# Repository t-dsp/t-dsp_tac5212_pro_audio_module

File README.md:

# T-DSP TAC5212 Pro Audio Module

**Part of the [T-DSP](https://t-dsp.com) open modular audio platform.**

A compact (50mm x 34.5mm) stereo audio codec module built around the **Texas Instruments TAC5212** high-performance audio codec.

| | |
|:---:|:---:|
|  |  |
|  |  |

**[View 3D Render Gallery](https://t-dsp.github.io/t-dsp_tac5212_pro_audio_module/gallery.html)** -- interactive slideshow of all board views

## About T-DSP

T-DSP is an open modular audio platform designed for musicians, engineers, and developers who want powerful digital signal processing in a flexible, hackable format. Built around the [Teensy](https://www.pjrc.com/teensy/) microcontroller and the [Teensy Audio Library](https://www.pjrc.com/teensy/td_libs_Audio.html), T-DSP combines studio-quality audio with a growing library of open-source modules for mixing, synthesis, effects, and more.

Whether you're building a custom digital mixer, crafting a unique instrument, or prototyping audio products, T-DSP gives you the tools to bring your ideas to life.

Join the community, contribute to the library, or grab a module and start patching. Learn more at [t-dsp.com](https://t-dsp.com).

## Overview

This codec module provides stereo ADC and DAC conversion and is one of the core building blocks of the T-DSP platform. It is designed as a **chip-on-board module** -- a complete, self-contained audio codec that solders directly onto a user-designed backplane PCB, just like any other component. A KiCad footprint is provided so you can drop the module into your own backplane design, add whatever jacks and connectors your application needs, and build a custom audio device without dealing with codec layout or analog design.

## Audio Capabilities

### Inputs (2 differential pairs)
- Line-level (consumer -10dBV or professional +4dBu)
- Instrument-level (guitar/bass) with external preamp/buffer (preamp and buffer modules are on the T-DSP project roadmap)
- Microphone (dynamic, with up to 12dB analog channel gain and additional digital gain)
- Programmable input impedance (5k/10k/40k ohm), DC-coupled. Optional 100k ohm bias resistors on board.
- 2 VRMS full-scale differential input

### Outputs (2 differential pairs)
- Headphone drive (16-300 ohm, 62.5mW @ 16 ohm, ~31mW @ 32 ohm)
- Consumer line out (-10dBV)
- Professional balanced output (+4dBu)
- 10 ohm output impedance, 2 VRMS differential output

## Digital Interface

- **I2S/PCM** audio data (DIN, DOUT, BCLK, LRCK, MCLK)
- **I2C** control bus for codec register configuration
- **GPIO** pins for additional control and sensing

The T-DSP platform is developed with [Teensy](https://www.pjrc.com/teensy/) and the [Teensy Audio Library](https://www.pjrc.com/teensy/td_libs_Audio.html), but the module uses standard I2S and I2C interfaces and can work with any compatible microcontroller or DSP platform.

## Modular Architecture

The module connects to your backplane via **2.54mm (0.1") header pins** (52 pins total), organized into functional groups. Headers can be male/female for a removable connection, or soldered permanently with straight pins:

- **DSP IO** (20 pins) -- digital audio (I2S), I2C control, MCLK, and power. Also available as a 20-pin ribbon header for off-board connection via standard ribbon cable.
- **Analog IO** (16 pins) -- stereo input and output pairs with analog ground references.
- **GPIO** (8 pins) -- additional I2C, general-purpose IO, and digital ground.
- **Power** (8 pins) -- 5V, 3.3V, MIC_BIAS, and ground lines.

### Backplane Integration

A KiCad footprint for the module is included in `/lib_fp/`, allowing you to import it directly into your own backplane PCB design. You handle the jacks, connectors, and mechanical layout on your backplane -- the module takes care of codec, filtering, and power regulation.

**Example backplanes built with the T-DSP module:**

### Module part (backplane)

Same method as the T-DSP core and the other modules: on a backplane the module is one part, **A1 `T-DSP_TAC5212`**
(`lib_sch/t-dsp_tac5212_pro_audio_module.kicad_sym`), with footprint `t-dsp_tac5212_pro_audio_module:T-DSP_TAC5212_Socket`
(`lib_fp/t-dsp_tac5212_pro_audio_module.pretty`, origin = module top-left, module outline on silk). Module 41.34 x 26.46 mm.
The module board itself keeps its own footprint (`board_outline108`, pads 1-52); the socket has the same pads, renumbered:

| Unit | Header | Pins | Module pads |
|---|---|---|---|
| A | J1 DSP IO (2x10, left edge) | 1 EN, 3 5V, 4 3V3_IO, 7 DIN, 9 DOUT, 11 BCLK, 13 LRCK, 15 DSP_SDA, 17 DSP_SCL, 19 MCLK, even pins GNDD (2, 5 NC) | 1-20 |
| B | J2 analog (2x9, top edge) | 1/3 OUT1P/M, 5/7 OUT2P/M, 9/11 IN1P/M, 13/15 IN2P/M, 17 MICBIAS, even pins AGND | 21-36, 48 |
| C | J3 codec I2C / GPIO (1x8, bottom edge) | 1 SCL, 2 SDA, 3 GNDD, 4 GPIO1, 5 GPIO2, 6 GPO1, 7 GPI1, 8 GNDD | 37-44 |
| D | H mounting holes (plated, 2.2 mm, M2) | H1 / H2 AGND side, H3 / H4 DGND side | 49-52 |

All header pins sit on one 2.54 mm grid (the socket snaps the module's pads by 0.01 mm or less). The four M2
standoffs carry the module. Generated by `scripts/build_tac5212_lib.py`.

### Multi-Module Chaining

Because the digital outputs are buffered on each module, multiple modules can run together on the same digital bus. You can daisy-chain modules in two ways:

- **On the backplane** -- route the digital bus as board traces between multiple module footprints.
- **Via ribbon cable** -- use a ribbon cable with multiple taps to connect up to 4 modules per chain.

System designers only need to focus on analog signal routing. The buffered digital bus works reliably over longer distances and across many modules.

## On-Board Circuitry

- LDO regulator for clean 3.3V analog power
- Buffered digital outputs for reliable backplane distribution
- TVS protection on audio outputs
- Ferrite bead RF filtering on audio inputs
- Solder jumpers for I2C address configuration
- Power indicator LED

The T-DSP platform has gone through several design iterations. The bench prototype below is from an earlier version of the project -- a different module architecture that helped shape the current design.

## Project Files

| Directory | Contents |
|-----------|----------|
| `/3d_models/` | 3D models for PCB components and enclosure |
| `/documentation/` | TAC5212 datasheets, [schematic PDF](documentation/t-dsp-tac5212-schematic.pdf), [footprint drawing](documentation/t-dsp-tac5212-footprint.pdf), and [3D model (STL)](documentation/t-dsp_tac5212_pro_audio_module.stl). View online: [schematic](https://kicanvas.org/?github=https://github.com/t-dsp/t-dsp_tac5212_pro_audio_module/blob/main/t-dsp_tac5212_pro_audio_module.kicad_sch) and [PCB layout](https://kicanvas.org/?github=https://github.com/t-dsp/t-dsp_tac5212_pro_audio_module/blob/main/t-dsp_tac5212_pro_audio_module.kicad_pcb) via KiCanvas |
| `/lib_fp/` | Custom KiCad footprint libraries |
| `/lib_sch/` | Custom KiCad schematic symbol libraries |
| `/pages/` | [3D Render Gallery](https://t-dsp.github.io/t-dsp_tac5212_pro_audio_module/gallery.html), [Interactive BOM](https://t-dsp.github.io/t-dsp_tac5212_pro_audio_module/ibom.html) |
| `/scripts/` | LCSC enrichment and BOM verification scripts |

## Building Manufacturing Files

Manufacturing files (gerbers, drill, BOMs, CPL, interactive BOM) are generated automatically by [KiBot](https://github.com/INTI-CMNB/KiBot) via GitHub Actions on every push to `main`. Download the ZIP from the **Actions** tab or from **Releases**.

The ZIP includes:
- Gerbers and drill files for any PCB fabricator
- JLCPCB BOM (`*_bom_JLCPCB.csv`) with LCSC part numbers
- Generic BOM (`*_bom_generic.csv`) with manufacturer part numbers
- Pick and place / CPL file
- Schematic PDF and PCB layout PDF
- Interactive BOM (also deployed live: [view iBOM](https://t-dsp.github.io/t-dsp_tac5212_pro_audio_module/ibom.html))

To build locally, install [Docker](https://www.docker.com/) and run:

```powershell
docker run --rm -v "${PWD}:/workspace" -w /workspace ghcr.io/inti-cmnb/kicad9_auto:latest kibot -c .kibot.yaml -b t-dsp_tac5212_pro_audio_module.kicad_pcb -e t-dsp_tac5212_pro_audio_module.kicad_sch -d manufacturing
```

Output files appear in `manufacturing/t-dsp_tac5212_pro_audio_module/`.

## Related Projects

Browse all T-DSP modules and backplanes on the [T-DSP GitHub organization](https://github.com/orgs/t-dsp/repositories).

## Status

This revision has not yet been built. The previous board was functional but had a few signal routing errors and needed a redesign of the analog output stage for low-impedance headphone drive. Those issues have been addressed in the current design.

If you build one, we'd love to hear how it goes -- please open an issue or reach out with your findings.

## Contact

For consulting, custom backplane design, or commercial licensing inquiries, reach out via [LinkedIn](https://linkedin.com/in/jayshoe).

## License

This project is licensed under the [Creative Commons Attribution-NonCommercial-ShareAlike 4.0 International (CC BY-NC-SA 4.0)](https://creativecommons.org/licenses/by-nc-sa/4.0/).

You are free to share and adapt this work for non-commercial purposes, as long as you give appropriate credit and distribute any derivatives under the same license.

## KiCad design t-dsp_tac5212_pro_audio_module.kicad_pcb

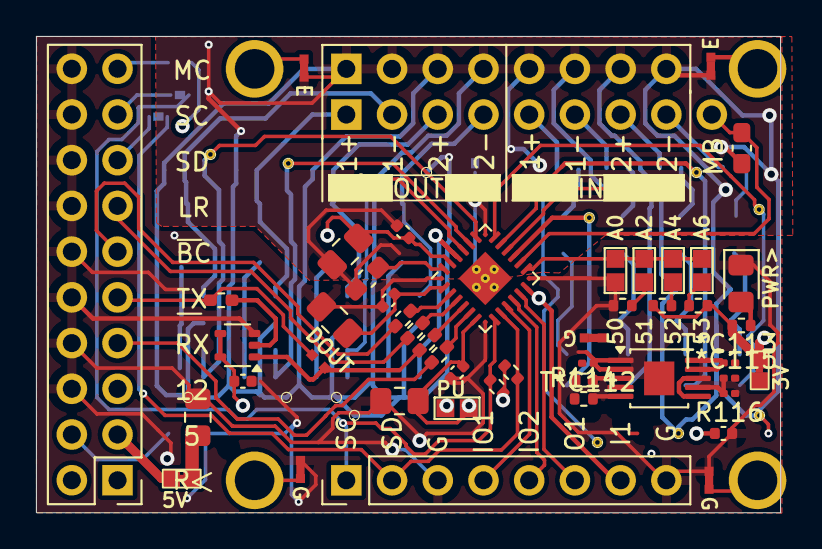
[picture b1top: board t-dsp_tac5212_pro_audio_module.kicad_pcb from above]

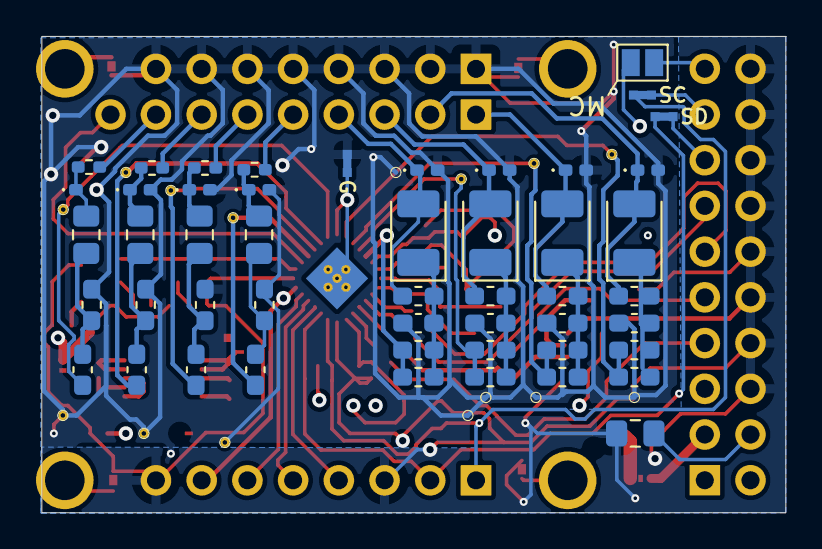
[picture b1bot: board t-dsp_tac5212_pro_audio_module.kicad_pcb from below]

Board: 4 copper layers, 41.3 x 26.5 mm, 117 parts (64 on the bottom side), 72 nets.

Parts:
ADD108: 0x50 | 0xA0; SolderJumper-2_Open_Pad0.5x1.0mm_ADDR
ADD110: 0x52 | 0xA4; SolderJumper-2_Open_Pad0.5x1.0mm_ADDR
ADD111: 0x53 | 0xA6; SolderJumper-2_Open_Pad0.5x1.0mm_ADDR
ADD112: 0x51 | 0xA2; SolderJumper-2_Open_Pad0.5x1.0mm_ADDR
C108, C111, C115, C131: 10uF; C_0805_2012Metric_Pad1.18x1.45mm_HandSolder
C109, C112, C116, C128, C129, C132: 0.1uF; C_0402_1005Metric
C110, C117, C121, C123: 47uF; CP_EIA-3528-21_Kemet-B_Pad1.50x2.35mm_HandSolder
C113, C114, C120, C122: 0.0047µF (4.7nF); C_0603_1608Metric_Pad1.08x0.95mm_HandSolder
C118, C119: 1uF; C_0603_1608Metric_Pad1.08x0.95mm_HandSolder
C124, C125, C126, C127: 10uF; C_0603_1608Metric_Pad1.08x0.95mm_HandSolder
C130: 47uF; C_0805_2012Metric_Pad1.15x1.40mm_HandSolder
D108, D109, D110, D111, D112, D113, D114, D115: TPD1E10B06DPYR; D_0402_1005Metric_Pad0.77x0.64mm_HandSolder
D116: RED LED; D_0805_2012Metric_custom
DOUT108: Jump DOUT1; jumper_slice_disconnected_alt-text
E108, E109: jumper; jumper_slice
FB108, FB109, FB110, FB111: BLM21A601S - BLM21AG601SH1; L_0805_2012Metric_Pad1.18x1.45mm_HandSolder
G109, G110, G111, G112: VIA; SMD_ROUTING_PAD
G113, G114, G116: VIA; via
G117, G118, G119: jumper; jumper_slice
G123: SMD ROUTING PAD; SMD_ROUTING_PAD
GND108: BRIDGE; jumper_slice
INM1, INM2: VIA; via
INP1, INP2: VIA; via
J3V108, J5V108: jumper; jumper_slice_1mm
MCLK108: jumper; SolderJumper-2_P1.3mm_Open_Pad1.0x1.5mm_Master_Clock
NT108, NT109, NT110: NetTie_2; NetTie-2_SMD_Pad0.2mm
OUTM1: VIA; via
OUTP1, OUTP2: VIA; via
PU_EN108: JUMPER; SolderJumper-2_Open_Pad0.5x1.0mm_PU
R108, R111, R132, R135: 10 ohm; R_0603_1608Metric_Pad1.05x0.95mm_HandSolder
R109, R110, R112, R113: 49.9; R_0402_1005Metric_Pad0.72x0.64mm_HandSolder
R114: 4.99k; R_0402_1005Metric
R115, R118, R119: 0 Ohm; R_0402_1005Metric_Pad0.72x0.64mm_HandSolder
R116: 33.2kΩ; C_0201_0603Metric
R117, R125: 33 ohm; R_0402_1005Metric_Pad0.72x0.64mm_HandSolder
R120, R121, R140: 2.21k ohm; R_0402_1005Metric
R122: 22.0k; R_0402_1005Metric
R123, R124: 4.7k; R_0402_1005Metric
R127, R128, R129, R130: DNP; R_0603_1608Metric_Pad1.05x0.95mm_HandSolder
R134, R161, R162, R163: 0 ohm; R_0603_1608Metric_Pad1.05x0.95mm_HandSolder
R136, R137, R138, R139: 100K; R_0603_1608Metric_Pad1.05x0.95mm_HandSolder
SCL108: jumper; jumper_slice
SDA108: jumper; jumper_slice
T108, T109, T110, T111: Tab
T*C112, T*C113, T*C115: 4.7uF; C_0201_0603Metric
TAC5212: TAC5212IRGER; VQFN-24-1EP_4x4mm_P0.5mm_EP2.45x2.45mm_ThermalVias
U108: Single Buffer with Tri-state Passthru - SN74LVC1G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; SOT-353_SC-70-5
U110: LT3042xMSE; MSOP-10-1EP_3x3mm_P0.5mm_EP1.68x1.88mm
board_outline108: board; audio_module_board_outline_50x34.5_e1

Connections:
3.3V_LDO: J3V108.1, NT109.1, R122.2, R123.2, R140.1
3.3V_THIN: C108.1, C109.1, NT109.2, TAC5212.23 (AVDD)
3.3v_IDE: C111.1, C112.1, C128.1, C131.1, PU_EN108.2, TAC5212.6 (IOVDD), U108.4 (OE^), U108.5 (VCC), board_outline108.4 (3.3V)
5V: C130.1, J5V108.1, NT108.1, NT110.1
5212_BCLK1: R119.1, board_outline108.11 (BCLK)
5212_DIN1: R118.1, board_outline108.7 (DSP_DOUT)
5212_DOUT1: DOUT108.1, R117.1, U108.1 (A)
5212_DOUT1+: DOUT108.2, R125.1, board_outline108.9 (DSP_DIN)
5212_LRCK1: R115.1, board_outline108.13 (LRCK)
5212_MCLK1: MCLK108.1, board_outline108.19 (MCLK)
5212_SCL: R121.1, SCL108.2, TAC5212.7 (SCL), board_outline108.37 (SCL)
5212_SDA: R120.1, SDA108.2, TAC5212.8 (SDA), board_outline108.38 (SDA)
DSP_SCL: SCL108.1, board_outline108.17 (SCL)
DSP_SDA: SDA108.1, board_outline108.15 (SDA)
EN_HELD_HIGH: C129.1, C132.1, U110.3 (EN/UV), board_outline108.1 (HELD_HIGH)
Earth: C108.2, C109.2, C113.2, C114.2, C118.2, C119.1, C120.2, C122.2, D108.2 (K), D109.2 (K), D110.2 (K), D111.2 (K), D112.2 (K), D113.2 (K), D114.2 (K), D115.2 (K), E108.1, E109.2, G109.1, G110.1, G111.1, G112.1, G113.1, G114.1, G116.1, G119.2, G123.1, GND108.2, R114.1, R116.1, R136.2, R137.2, R138.2, R139.2, T*C112.2, T*C113.2, T*C115.2, U110.6 (PGFB), U110.8 (GND), U110.11 (GND), board_outline108.22 (AGND), board_outline108.24 (AGND), board_outline108.26 (AGND), board_outline108.28 (AGND), board_outline108.30 (AGND), board_outline108.32 (AGND), board_outline108.34 (AGND), board_outline108.36 (AGND)
GNDD: ADD108.1, C111.2, C112.2, C115.2, C116.2, C128.2, C129.2, C130.2, C131.2, C132.2, D116.1 (K), G117.2, G118.2, GND108.1, R124.2, TAC5212.25 (VSS), TAC5212.A1 (VSS), TAC5212.A2 (VSS), TAC5212.A3 (VSS), TAC5212.A4 (VSS), U108.3 (GND), board_outline108.6 (GNDD), board_outline108.8 (GNDD), board_outline108.10 (GNDD), board_outline108.12 (GNDD), board_outline108.14 (GNDD), board_outline108.16 (GNDD), board_outline108.18 (GNDD), board_outline108.20 (GNDD), board_outline108.39 (GNDD), board_outline108.44 (GNDD)
GPI1: MCLK108.2, TAC5212.12 (GPI1), board_outline108.43 (GPI1)
GPIO1: TAC5212.9 (GPIO1), board_outline108.40 (GPIO1)
GPIO2: TAC5212.10 (GPIO2), board_outline108.41 (GPIO2)
GPO1: TAC5212.11 (GPO1), board_outline108.42 (GPO1)
IN1M: C126.2, INM1.1, TAC5212.16 (IN1M)
IN1M+: R112.2, board_outline108.31 (IN1M)
IN1P: C127.2, INP1.1, TAC5212.15 (IN1P)
IN1P+: R113.2, board_outline108.29 (IN1P)
IN2M: C124.2, INM2.1, TAC5212.18 (IN2M)
IN2M+: R110.2, board_outline108.35 (IN2M)
IN2P: C125.2, INP2.1, TAC5212.17 (IN2P)
IN2P+: R109.2, board_outline108.33 (IN2P)
MICBIAS: C118.1, TAC5212.14 (MICBIAS), board_outline108.48 (MIC_BIAS)
unnamed: ADD110.1, R122.1
unnamed: ADD111.1, R123.1
unnamed: ADD112.1, R124.1
unnamed: C110.1, C113.1, R108.1, R127.1, R161.2
unnamed: C114.1, C117.1, R111.1, R128.1, R162.2
unnamed: C120.1, C121.1, R129.1, R132.1, R163.2
unnamed: C122.1, C123.1, R130.1, R134.2, R135.1
unnamed: C124.1, FB108.2, R136.1
unnamed: C125.1, FB109.2, R137.1
unnamed: C126.1, FB110.2, R138.1
unnamed: C127.1, FB111.2, R139.1
unnamed: D112.1 (K), FB108.1, R110.1
unnamed: D113.1 (K), FB109.1, R109.1
unnamed: D114.1 (K), FB110.1, R112.1
unnamed: D115.1 (K), FB111.1, R113.1
unnamed: D116.2 (A), R140.2
unnamed: E108.2, board_outline108.49 (AGND)
unnamed: E109.1, board_outline108.50 (AGND)
unnamed: G117.1, board_outline108.51 (DGND)
unnamed: G118.1, board_outline108.52 (DGND)
unnamed: NT110.2, T*C112.1, U110.1 (IN), U110.2 (IN)
unnamed: PU_EN108.1, R120.2, R121.2
unnamed: ADD108.2, ADD110.2, ADD111.2, ADD112.2, TAC5212.13 (ADDR)
unnamed: R119.2, TAC5212.2 (BCLK)
unnamed: R118.2, TAC5212.5 (DIN)
unnamed: R117.2, TAC5212.4 (DOUT)
unnamed: C115.1, C116.1, TAC5212.1 (DREG)
unnamed: R115.2, TAC5212.3 (FSYNC)
unnamed: C119.2, TAC5212.24 (VREF)
unnamed: R125.2, U108.2 (B)
unnamed: R114.2, U110.5 (ILIM)
unnamed: T*C113.1, U110.9 (OUTS), U110.10 (OUT)
unnamed: R116.2, T*C115.1, U110.7 (SET)
unnamed: J5V108.2, board_outline108.3 (5V)
OUT1M: OUTM1.1, R111.2, R128.2, TAC5212.19 (OUT1M)
OUT1M+: C117.2, D109.1 (K), R162.1, board_outline108.23 (OUT1M)
OUT1P: OUTP1.1, R108.2, R127.2, TAC5212.20 (OUT1P)
OUT1P+: C110.2, D108.1 (K), R161.1, board_outline108.21 (OUTP)
OUT2M: R130.2, R135.2, TAC5212.22 (OUT2M)
OUT2M+: C123.2, D111.1 (K), R134.1, board_outline108.27 (OUT2M)
OUT2P: OUTP2.1, R129.2, R132.2, TAC5212.21 (OUT2P)
OUT2P+: C121.2, D110.1 (K), R163.1, board_outline108.25 (OUT2P)

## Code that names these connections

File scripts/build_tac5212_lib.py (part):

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           'DSP_SDA', 'GNDD', 'DSP_SCL', 'GNDD', 'MCLK', 'GNDD'],
    'J2': ['OUT1P', 'AGND', 'OUT1M', 'AGND', 'OUT2P', 'AGND', 'OUT2M', 'AGND', 'IN1P', 'AGND', 'IN1M', 'AGND',
           'IN2P', 'AGND', 'IN2M', 'AGND', 'MICBIAS'],
    'J3': ['SCL', 'SDA', 'GNDD', 'GPIO1', 'GPIO2', 'GPO1', 'GPI1', 'GNDD'],
}
PAD_SIZE, PAD_DRILL = 1.7, 1.0
SILK_OFF = 1.33
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
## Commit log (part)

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2024-08-25 added enable (held-high)
2024-12-24 2024-12-23_T-DSP_TAC5212_V0.5.1
2024-12-24 2024-12-23_T-DSP_TAC5212_V0.5.12
2025-01-06 update after a few builds.
    The 3.3v pin on the T-DSP connector is incorrect.
2025-01-07 update the module io for the 3v from digital audio board v1
2025-04-21 adding documentation
2025-04-21 finish wqfn
2025-08-20 fix net ties and 28 pin wqfn-28
2025-08-20 create fabrication outputs
2025-08-20 working on production
2025-08-20 update fab
2025-08-21 fab update
2026-02-07 Prepare repo for public release under CC BY-NC-SA 4.0 - Add LICENSE file (CC BY-NC-SA 4.0) and README with T-DSP project description, audio specs, modular architecture, and pinout diagram - Remove th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
2026-02-07 Update README: clarify module form factor and backplane integration
2026-02-07 Rename project to T-DSP TAC5212 Pro Audio Module
    - Rename all KiCad project files from tac5212_audio_board_single_ended
    to t-dsp_tac5212_pro_audio_module
    - Update internal filename references in .kicad_pro and .kicad_prl
    - Rename schematic/footprint PDFs and move to documentation/
    - Update README: new title, corrected connector/module descriptions,
    add 3D renders, pinout diagram, interactive BOM link, and docs links
2026-02-07 Add backplane example images to README
2026-02-07 Add hardware photos to README
    - Bare module photo (top and bottom) as hero image
    - Real backplane prototype photo
    - Rack-mounted bench prototype photo
2026-02-07 Update bench photo caption to reference T-DSP platform
2026-02-07 Add contact section with LinkedIn for consulting inquiries
2026-02-07 Rename documentation files to lowercase and add footprint image
2026-02-07 Add context for earlier bench prototype photo
2026-02-07 Add project status section to README
2026-02-07 Add Teensy and Teensy Audio Library references with links
2026-02-08 Fix README audio specs against TAC5212 datasheet
    Correct gain claim (12dB analog, not 60dB), input impedance
    (programmable 5k/10k/40k, not 100k), headphone power (62.5mW@16ohm,
    ~31mW@32ohm), output swing (2 VRMS differential), and label I/O as
    differential pairs.
2026-02-08 Correct README audio input specs
    Fix input voltage range to 2 VRMS differential, clarify instrument
    input requires external preamp/buffer, note preamp modules on roadmap.
2026-02-08 Add KiCanvas links for online schematic and PCB viewing
2026-02-08 Add Related Projects section linking to T-DSP GitHub org
2026-02-08 Add interactive 3D model (STL) export of PCB
    Exported via kicad-cli. GitHub renders STL files interactively in the
    browser.
2026-02-08 planing for kibot
2026-02-09 fix all drc errors.
2026-02-09 Add KiBot CI/CD pipeline for JLCPCB manufacturing files
    - Add .kibot.yaml config for gerbers, drill, BOM, CPL, and ZIP output
    - Add GitHub Actions workflow triggered on push to main and manual dispatch
    - Add release job to attach JLCPCB ZIP to GitHub Releases on version tags
    - Fix malformed reference designators (5V108, 3V108) that blocked KiBot BOM/CPL
    - Add local build instructions to README
2026-02-09 Fix workflow to trigger on version tags
    Add tags filter so tag pushes (e.g. v0.92) trigger the release job.
2026-02-09 Add LCSC part number for U108 (SN74LVC1G66DCK)
    Add C113518 to complete JLCPCB BOM coverage for all active components.
2026-02-09 Add generic BOM output for PCBWay and other fab houses
    Includes Manufacturer, MPN, Package, LCSC, Digikey, Mouser, and Description
    columns. Also uploaded as a separate artifact and attached to releases.
2026-02-09 Add LCSC enrichment, iBOM, and consolidate manufacturing pipeline
    - Enrich schematic with LCSC_Manufacturer and LCSC_MPN for all components
    - Add enrichment and verification scripts (scripts/)
    - Consolidate all outputs into single project-named folder
    - Both BOMs (JLCPCB + generic with MPN) included in manufacturing ZIP
    - Add interactive BOM generation and GitHub Pages deployment
    - Remove deprecated gerber/, bom/, and panel/ folders (replaced by CI)
2026-02-09 Skip Pages deployment on tag pushes (only deploy from main)
2026-02-09 Fix Package field conflicts and enable gerber job file
    - C128: Package C0603 → C0402 (matches footprint)
    - C124: Package C0805 → C0603 (matches footprint)
    - Enable gerber job file for automatic layer identification by fabs
2026-02-09 Add schematic and PCB layout PDFs to manufacturing output
2026-02-09 Fix BOM field conflicts and component data errors
    - Fix R126 LCSC code (C60491 100K -> C138019 2.21K) in schematic and PCB
    - Fix Package/Case mismatches in PCB: C128 (C0603->C0402), C124 (C0805->C0603)
    - Fix Description fields: remove MISMATCH FOOTPRINT notes, correct 0603->0402
    for R122, R123, R124; unify R125 description to match R117
    - Fix D116 LED Package/Case from 1206(CHECKME) to 0805
    - Add schematic PDF and PCB layout PDF to manufacturing ZIP
2026-02-09 Add version, date, and license to manufacturing outputs
    - Add KiBot preflight to auto-populate REVISION (git tag) and DATE variables
    - Replace static "V0.91" silkscreen text with ${REVISION} variable
    - Add schematic title block with date, revision, copyright, and CC BY-NC-SA license
    - Remove reference designator printing from gerber silkscreen and PCB PDF
    - Hide footprint refs on F.Cu, F.SilkS, B.Cu, B.SilkS in PCB PDF output
2026-02-09 Enable update_pcb_text_cache for silkscreen text variable resolution
    KiCad 9 does not re-resolve ${REVISION} on silkscreen after cache
    invalidation. Use update_pcb_text_cache to write resolved values
    directly into the PCB's text variable cache.
2026-02-09 Add version to ZIP filename and PCB title block
    - Add PCB title_block with ${REVISION} so %r resolves in output filenames
    - ZIP now named t-dsp_tac5212_pro_audio_module-manufacturing_v0.98.zip etc.
2026-02-10 Add auto-generated PCB spec to manufacturing ZIP
    Adds a KiBot report output that generates board specifications
    (dimensions, layer stackup, materials, track/drill specs) from
    PCB metadata. Included in the manufacturing ZIP for manufacturer
    reference.
2026-02-10 Add 3D renders, hide ref designators, fix legacy 3D model paths
    - Add Blender 3D render output (8 views: top, bottom, 4 sides, 2 isometric)
    to KiBot config and manufacturing ZIP
    - Split CI workflow into 3 steps: manufacturing outputs, 3D renders
    (kicad9_auto_full), and ZIP packaging
    - Add PCB spec report to manufacturing outputs
    - Hide reference designators and component values from silkscreen
2026-02-10 Fix release upload for re-tagged versions
    Replace softprops/action-gh-release with gh release upload --clobber
    so re-tagging a version overwrites the existing ZIP instead of failing
    with "Too many retries".
2026-02-10 Fix release upload: add --repo flag for gh CLI
    The release job has no checkout step, so gh CLI can't infer the repo
    from git. Pass --repo explicitly.
2026-02-24 Add 3D render gallery, update schematic for production
    - Add interactive 3D render gallery with All Components / SMD Only tabs
    - Add gallery.html page deployed to GitHub Pages alongside iBOM
    - Update KiBot config: _th_ prefix file_ids, exclude_tht filter, 3d_renders_smd output
    - Update CI workflow to deploy renders and gallery to GitHub Pages
    - Update README with gallery thumbnail grid and links
    - Schematic updates: 49.9Ω ADC input resistors, 100K bias pull-downs, component refinements
2026-02-24 Fix release job: create release before uploading assets
    Match desktop_pro pattern: gh release create before upload, rename ZIP
    with tag version.
2026-03-10 Shrink board size to match Teensy audio adaptor shield dimensions
    Update board outline width (42mm → 41.34mm), add connector 3D models
    for pin sockets, and refresh PCB layout.
